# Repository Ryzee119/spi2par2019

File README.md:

# spi2par2019
  
## What is it?
This is a recreation of a legacy Original Xbox adaptor that allowed you to use extremely common and cheap HD44780 compliant character LCD displays with the Xenium modchip SPI interface. The legacy adaptor was called 'spi2par' and has long since been out of production and extremely hard to come by.

I have never had one either, so this design has been made from the ground up.

There are two PCB layouts in this repository:

1. More faithful to the legacy spi2par design.
2. An LCD backpack design that takes advantage of the standard pinout of most HD44780 LCD displays to minimise the amount of wiring needed.

These two layouts are shown in the below photo. The LCD backpack has two pin arrangements so can be used on the two common LCD pin header layouts as shown installed. The intent is to make this as open and easily accessible to anyone with minimal experience in soldering and programming.  

## Features
1. Converts the Xenium SPI interface to HD44780 compliant parallel LCDs. These are extremely cheap and readily available LCD modules.
2. Software controllable brightness
3. Software controllable contrast
4. This feature never existed in the legacy. You can connect two additional wires to the motherboard LPC header, and the board will read fan speed and MB/CPU temperatures directly from the Xbox System Management bus. It will display and update this mid-game. Traditionally the LCD will just pause until you renter the dashboard.  Example below:  

## Assembly and Materials Required
There is two ways you can do this. Option 1 is the intended way and has a PCB daughter board to make installation easier.  <br> The second option uses less components but requires more wiring.

#### Option 1 - Arduino module and PCB adaptor
The standard design

|Part|Qty | Possible Source|
|--|--|--|
| Ryzee119's spi2par2019 PCB |1| OSHPark (Bit expensive, 3 boards):  [spi2par2019backpack](https://oshpark.com/shared_projects/HGCRYTFI) OR<br> [spi2par2019faithful](https://oshpark.com/shared_projects/7YvM7Fwu)  <br>Or, Download the required zip file from the [Gerbers Folder](https://github.com/Ryzee119/spi2par2019/tree/master/hardware/gerbers) and upload the zip file to their online ordering service. Use the following PCB properties: <br> `2 layers, 45x30mm, 1.6mm thick, HASL, 1oz copper, no castellated holes`| 
| Arduino Pro Micro Leonardo 5V/16Mhz |1| [Any clones will work](https://www.aliexpress.com/item/New-Pro-Micro-for-arduino-ATmega32U4-5V-16MHz-Module-with-2-row-pin-header-For-Leonardo/32768308647.html). Make sure they're the 5V/16Mhz variant. | 
| N-Channel MOSFET 2N7002 SOT23 at position Q1| 1 |Find anywhere convenient <br> [Digikey](https://www.digikey.com.au/short/p4zbn8)<br> [Aliexpress](https://www.aliexpress.com/item/Free-Shipping-200PCS-2N7002-MOSFET-N-CH-60V-300MA-SOT-23/897983645.html) |
| JST SH1.0 10 pin 1mm connector (To connect to Xenium) | 1 |Digikey: [Connector](https://www.digikey.com.au/product-detail/en/jst-sales-america-inc/SHR-10V-S-B/455-1385-ND/759874) + 3x[Jumpers](https://www.digikey.com.au/product-detail/en/jst-sales-america-inc/ASSHSSH28K152/455-3076-ND/6009452) OR <br> Aliexpress: [Connector with Jumpers (Get the 10P one)](https://www.aliexpress.com/item/5PCS-100MM-SH-1-0-Wire-Cable-Connector-DIY-SH1-0-JST-2-3-4-5/32952366214.html)|
| General Hook-up Wire 26AWG or so| A metre or two |-|

#### Option 2 - Arduino module only
No extra PCB required, no backlight control, slightly harder soldering

|Part|Qty | Possible Source|
|--|--|--|
| Arduino Pro Micro Leonardo 5V/16Mhz |1| [Any clones will work](https://www.aliexpress.com/item/32768308647.html). Make sure they're the 5V/16Mhz variant. | 
| JST SH1.0 10 pin 1mm connector (To connect to Xenium) | 1 |Digikey: [Connector](https://www.digikey.com.au/product-detail/en/jst-sales-america-inc/SHR-10V-S-B/455-1385-ND/759874) + 3x[Jumpers](https://www.digikey.com.au/product-detail/en/jst-sales-america-inc/ASSHSSH28K152/455-3076-ND/6009452) OR <br> Aliexpress: [Connector with Jumpers (Get the 10P one)](https://www.aliexpress.com/item/32952366214.html)|
| General Hook-up Wire 26AWG or so| A metre or two |-|

## Programming
1. Clone this repository to your PC
2. Download then install the [Arduino IDE](https://www.arduino.cc/en/Main/Software).
3. Copy `spi2par2019` to your Sketch folder and open the `.ino` file.
4. Set the Board Type the `Arduino Leonardo` and the comport correctly.
5. Compile by clicking the tick in the top left.
5. Confirm it has compiled successfully from the console output.  
6. Connect a MicroUSB cable between the Arduino Module and the PC.   
7. Click the upload button and confirm successful. The LCD backlight should come on but no text will be displayed until connected to a Xenium or the Xbox SMBus.

## Installation

## Alternative Installation

## Further Setup
If using XBMC, there appears to be a bug in the way the large text is printed to the LCD screen when used with a Xenium. This can cause the LCD screen to stop working when the screen saver starts.
It is recommended to edit the /system/UserData/LCD.xml file and replace instances of `LCD.TimeWide21` or `LCD.TimeWide22` with something different. Perhaps `LCD.cputemperature` and `LCD.gputemperature` or if you want time, use the standard font (`System.Time`).

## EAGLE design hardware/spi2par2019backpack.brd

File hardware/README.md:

# spi2par2019

All PCBs have been design using [Autodesk Eagle](https://www.autodesk.com/products/eagle/free-download) software.
This has been released as open source hardware released under the CERN Open Hardware Licence v1.2, <br><br><br>

CERN Open Hardware Licence v1.2 

Preamble

Through this CERN Open Hardware Licence ("CERN OHL") version 1.2, CERN
wishes to provide a tool to foster collaboration and sharing among
hardware designers.  The CERN OHL is copyright CERN. Anyone is welcome
to use the CERN OHL, in unmodified form only, for the distribution of
their own Open Hardware designs. Any other right is reserved. Release
of hardware designs under the CERN OHL does not constitute an
endorsement of the licensor or its designs nor does it imply any
involvement by CERN in the development of such designs.

1. Definitions

In this Licence, the following terms have the following meanings:
 
“Licence” means this CERN OHL.

“Documentation” means schematic diagrams, designs, circuit or circuit
board layouts, mechanical drawings, flow charts and descriptive text,
and other explanatory material that is explicitly stated as being made
available under the conditions of this Licence. The Documentation may
be in any medium, including but not limited to computer files and
representations on paper, film, or any other media.

“Documentation Location” means a location where the Licensor has
placed Documentation, and which he believes will be publicly
accessible for at least three years from the first communication to
the public or distribution of Documentation.

“Product” means either an entire, or any part of a, device built using
the Documentation or the modified Documentation.

“Licensee” means any natural or legal person exercising rights under
this Licence.

“Licensor” means any natural or legal person that creates or modifies
Documentation and subsequently communicates to the public and/ or
distributes the resulting Documentation under the terms and conditions
of this Licence.

A Licensee may at the same time be a Licensor, and vice versa. 

Use of the masculine gender includes the feminine and neuter genders
and is employed solely to facilitate reading.

2. Applicability

2.1. This Licence governs the use, copying, modification,
communication to the public and distribution of the Documentation, and
the manufacture and distribution of Products. By exercising any right
granted under this Licence, the Licensee irrevocably accepts these
terms and conditions.

2.2. This Licence is granted by the Licensor directly to the Licensee,
and shall apply worldwide and without limitation in time. The Licensee
may assign his licence rights or grant sub-licences.

2.3. This Licence does not extend to software, firmware, or code
loaded into programmable devices which may be used in conjunction with
the Documentation, the modified Documentation or with Products, unless
such software, firmware, or code is explicitly expressed to be subject
to this Licence. The use of such software, firmware, or code is
otherwise subject to the applicable licence terms and conditions.

3. Copying, modification, communication to the public and distribution
of the Documentation

3.1. The Licensee shall keep intact all copyright and trademarks
notices, all notices referring to Documentation Location, and all
notices that refer to this Licence and to the disclaimer of warranties
that are included in the Documentation. He shall include a copy
thereof in every copy of the Documentation or, as the case may be,
modified Documentation, that he communicates to the public or
distributes.

3.2. The Licensee may copy, communicate to the public and distribute
verbatim copies of the Documentation, in any medium, subject to the
requirements specified in section 3.1.

3.3. The Licensee may modify the Documentation or any portion thereof
provided that upon modification of the Documentation, the Licensee
shall make the modified Documentation available from a Documentation
Location such that it can be easily located by an original Licensor
once the Licensee communicates to the public or distributes the
modified Documentation under section 3.4, and, where required by
section 4.1, by a recipient of a Product. However, the Licensor shall
not assert his rights under the foregoing proviso unless or until a
Product is distributed.

3.4. The Licensee may communicate to the public and distribute the
modified Documentation (thereby in addition to being a Licensee also
becoming a Licensor), always provided that he shall:

a) comply with section 3.1;

b) cause the modified Documentation to carry prominent notices stating
that the Licensee has modified the Documentation, with the date and
description of the modifications;

c) cause the modified Documentation to carry a new Documentation
Location notice if the original Documentation provided for one;

d) make available the modified Documentation at the same level of
abstraction as that of the Documentation, in the preferred format for
making modifications to it (e.g. the native format of the CAD tool as
applicable), and in the event that format is proprietary, in a format
viewable with a tool licensed under an OSI-approved license if the
proprietary tool can create it; and

e) license the modified Documentation under the terms and conditions
of this Licence or, where applicable, a later version of this Licence
as may be issued by CERN.

3.5. The Licence includes a non-exclusive licence to those patents or
registered designs that are held by, under the control of, or
sub-licensable by the Licensor, to the extent necessary to make use of
the rights granted under this Licence. The scope of this section 3.5
shall be strictly limited to the parts of the Documentation or
modified Documentation created by the Licensor.

4. Manufacture and distribution of Products

4.1. The Licensee may manufacture or distribute Products always
provided that, where such manufacture or distribution requires a
licence under this Licence the Licensee provides to each recipient of
such Products an easy means of accessing a copy of the Documentation
or modified Documentation, as applicable, as set out in section 3.

4.2. The Licensee is invited to inform any Licensor who has indicated
his wish to receive this information about the type, quantity and
dates of production of Products the Licensee has (had) manufactured

5. Warranty and liability

5.1. DISCLAIMER – The Documentation and any modified Documentation are
provided "as is" and any express or implied warranties, including, but
not limited to, implied warranties of merchantability, of satisfactory
quality, non-infringement of third party rights, and fitness for a
particular purpose or use are disclaimed in respect of the
Documentation, the modified Documentation or any Product. The Licensor
makes no representation that the Documentation, modified
Documentation, or any Product, does or will not infringe any patent,
copyright, trade secret or other proprietary right. The entire risk as
to the use, quality, and performance of a Product shall be with the
Licensee and not the Licensor. This disclaimer of warranty is an
essential part of this Licence and a condition for the grant of any
rights granted under this Licence. The Licensee warrants that it does
not act in a consumer capacity.

5.2. LIMITATION OF LIABILITY – The Licensor shall have no liability
for direct, indirect, special, incidental, consequential, exemplary,
punitive or other damages of any character including, without
limitation, procurement of substitute goods or services, loss of use,
data or profits, or business interruption, however caused and on any
theory of contract, warranty, tort (including negligence), product
liability or otherwise, arising in any way in relation to the
Documentation, modified Documentation and/or the use, manufacture or
distribution of a Product, even if advised of the possibility of such
damages, and the Licensee shall hold the Licensor(s) free and harmless
from any liability, costs, damages, fees and expenses, including
claims by third parties, in relation to such use.

6. General

6.1. Except for the rights explicitly granted hereunder, this Licence
does not imply or represent any transfer or assignment of intellectual
property rights to the Licensee.

6.2. The Licensee shall not use or make reference to any of the names
(including acronyms and abbreviations), images, or logos under which
the Licensor is known, save in so far as required to comply with
section 3. Any such permitted use or reference shall be factual and
shall in no event suggest any kind of endorsement by the Licensor or
its personnel of the modified Documentation or any Product, or any
kind of implication by the Licensor or its personnel in the
preparation of the modified Documentation or Product.

6.3. CERN may publish updated versions of this Licence which retain
the same general provisions as this version, but differ in detail so
far this is required and reasonable. New versions will be published
with a unique version number.

6.4. This Licence shall terminate with immediate effect, upon written
notice and without involvement of a court if the Licensee fails to
comply with any of its terms and conditions, or if the Licensee
initiates legal action against Licensor in relation to this
Licence. Section 5 shall continue to apply.

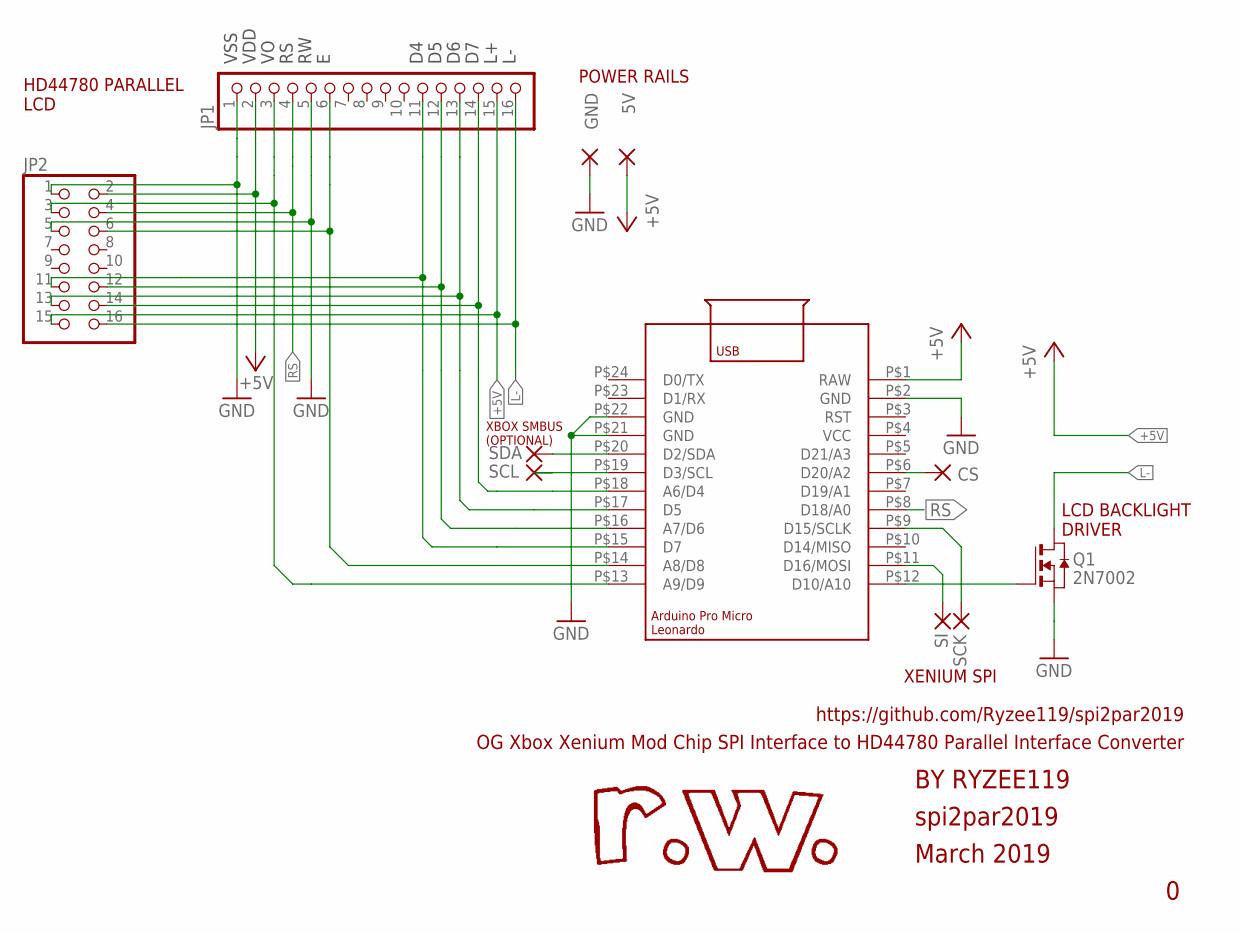
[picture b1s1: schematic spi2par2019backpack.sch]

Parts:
5V: WIREPADSMD1,27-254; SMD1,27-2,54
CS: WIREPADSMD1,27-254; SMD1,27-2,54
GND: WIREPADSMD1,27-254; SMD1,27-2,54
JP1: PINHD-1X16; 1X16
JP2: PINHD-2X8; 2X08
Q1: 2N70026Ω; SOT-23
SCK: WIREPADSMD1,27-254; SMD1,27-2,54
SCL: WIREPADSMD1,27-254; SMD1,27-2,54
SDA: WIREPADSMD1,27-254; SMD1,27-2,54
SI: WIREPADSMD1,27-254; SMD1,27-2,54
U1: ARDUINO_LEONARDO_MICRO

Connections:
+5V: 5V.1, JP1.2, JP1.15, JP2.2, JP2.15, U1.P$1 (RAW)
D4: JP1.11, JP2.11, U1.P$15 (D7)
D5: JP1.12, JP2.12, U1.P$16 (A7/D6)
D6: JP1.13, JP2.13, U1.P$17 (D5)
D7: JP1.14, JP2.14, U1.P$18 (A6/D4)
E: JP1.6, JP2.6, U1.P$14 (A8/D8)
GND: GND.1, JP1.1, JP1.5, JP2.1, JP2.5, Q1.2 (S), U1.P$2 (GND), U1.P$21 (GND), U1.P$22 (GND)
L-: JP1.16, JP2.16, Q1.1 (D)
unnamed: SCL.1, U1.P$19 (D3/SCL)
unnamed: CS.1, U1.P$6 (D20/A2)
unnamed: SCK.1, U1.P$9 (D15/SCLK)
unnamed: SI.1, U1.P$11 (D16/MOSI)
unnamed: Q1.3 (G), U1.P$12 (D10/A10)
unnamed: SDA.1, U1.P$20 (D2/SDA)
RS: JP1.4, JP2.4, U1.P$8 (D18/A0)
VO: JP1.3, JP2.3, U1.P$13 (A9/D9)

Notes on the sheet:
spi2par2019
March 2019
BY RYZEE119
OG Xbox Xenium Mod Chip SPI Interface to HD44780 Parallel Interface Converter
https://github.com/Ryzee119/spi2par2019
HD44780 PARALLEL LCD
POWER RAILS
LCD BACKLIGHT DRIVER
XENIUM SPI
XBOX SMBUS (OPTIONAL)
2N7002
VSS
VDD

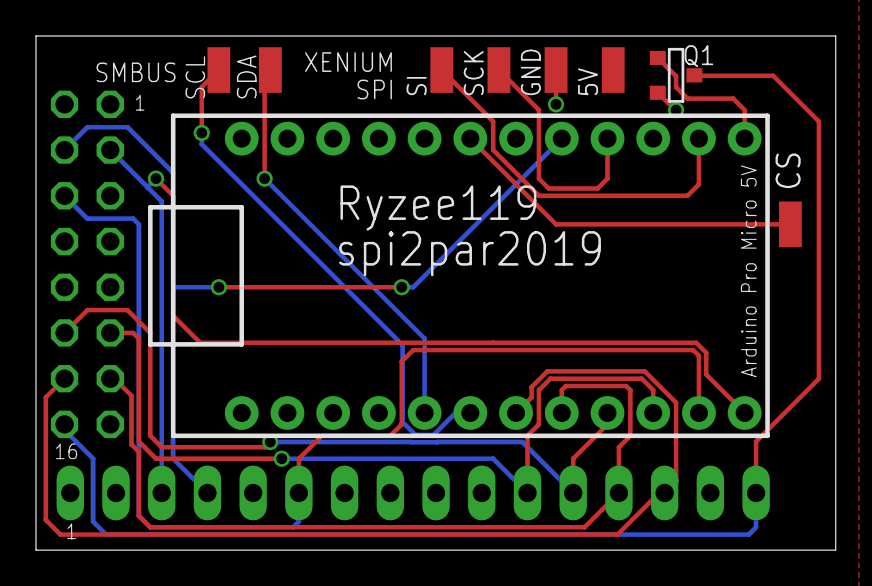
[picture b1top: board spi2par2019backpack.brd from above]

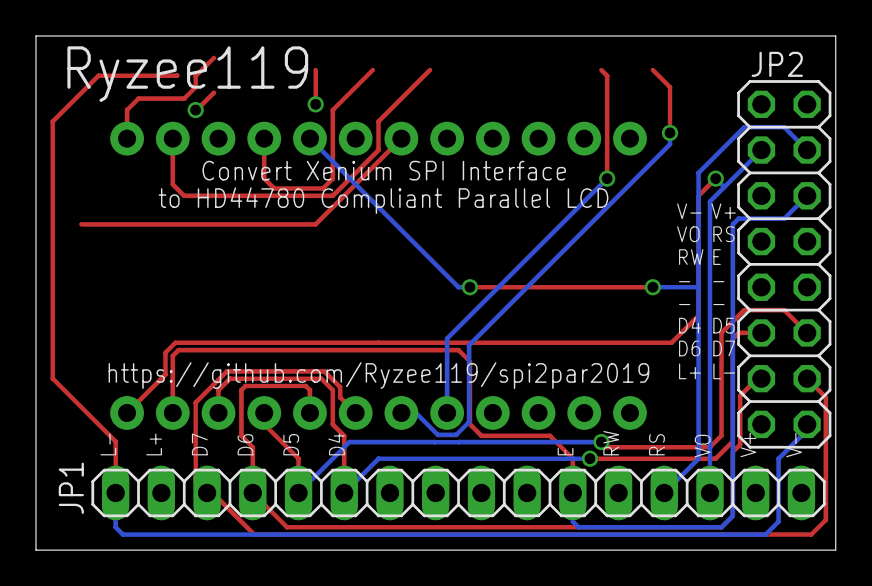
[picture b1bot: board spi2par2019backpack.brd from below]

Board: 2 copper layers, 44.4 x 28.6 mm, 11 parts (2 on the bottom side), 16 nets.

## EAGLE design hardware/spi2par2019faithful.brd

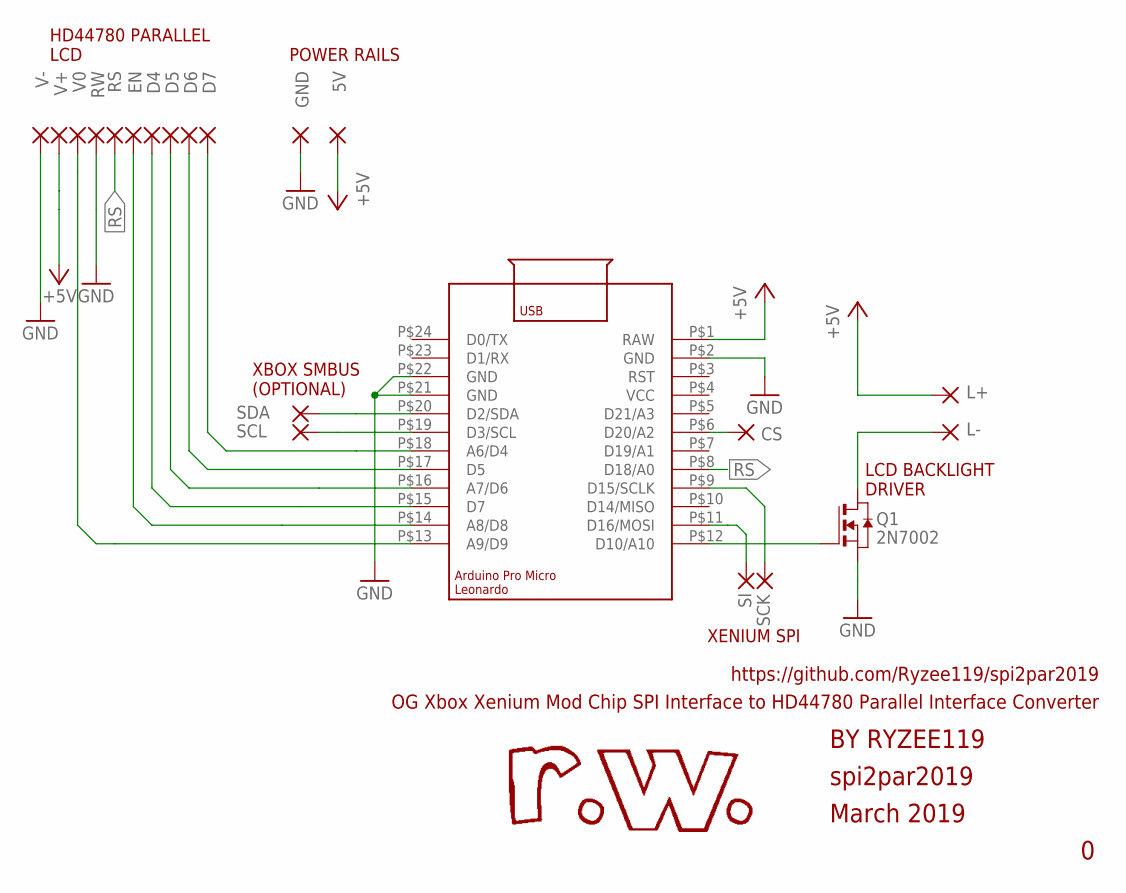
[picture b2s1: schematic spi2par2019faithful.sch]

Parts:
5V: WIREPADSMD1,27-254; SMD1,27-2,54
CS: WIREPADSMD1,27-254; SMD1,27-2,54
D4, D5, D6, D7: WIREPADSMD1,27-254; SMD1,27-2,54
EN: WIREPADSMD1,27-254; SMD1,27-2,54
GND: WIREPADSMD1,27-254; SMD1,27-2,54
L+: WIREPADSMD1,27-254; SMD1,27-2,54
L-: WIREPADSMD1,27-254; SMD1,27-2,54
Q1: 2N70026Ω; SOT-23
RS: WIREPADSMD1,27-254; SMD1,27-2,54
RW: WIREPADSMD1,27-254; SMD1,27-2,54
SCK: WIREPADSMD1,27-254; SMD1,27-2,54
SCL: WIREPADSMD1,27-254; SMD1,27-2,54
SDA: WIREPADSMD1,27-254; SMD1,27-2,54
SI: WIREPADSMD1,27-254; SMD1,27-2,54
U1: ARDUINO_LEONARDO_MICRO
V0: WIREPADSMD1,27-254; SMD1,27-2,54
V+: WIREPADSMD1,27-254; SMD1,27-2,54
V-: WIREPADSMD1,27-254; SMD1,27-2,54

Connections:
+5V: 5V.1, L+.1, U1.P$1 (RAW), V+.1
GND: GND.1, Q1.2 (S), RW.1, U1.P$2 (GND), U1.P$21 (GND), U1.P$22 (GND), V-.1
unnamed: SCL.1, U1.P$19 (D3/SCL)
unnamed: CS.1, U1.P$6 (D20/A2)
unnamed: SCK.1, U1.P$9 (D15/SCLK)
unnamed: SI.1, U1.P$11 (D16/MOSI)
unnamed: D7.1, U1.P$18 (A6/D4)
unnamed: D6.1, U1.P$17 (D5)
unnamed: D5.1, U1.P$16 (A7/D6)
unnamed: D4.1, U1.P$15 (D7)
unnamed: EN.1, U1.P$14 (A8/D8)
unnamed: Q1.3 (G), U1.P$12 (D10/A10)
unnamed: U1.P$13 (A9/D9), V0.1
unnamed: L-.1, Q1.1 (D)
unnamed: SDA.1, U1.P$20 (D2/SDA)
RS: RS.1, U1.P$8 (D18/A0)

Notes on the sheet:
spi2par2019
March 2019
BY RYZEE119
OG Xbox Xenium Mod Chip SPI Interface to HD44780 Parallel Interface Converter
https://github.com/Ryzee119/spi2par2019
HD44780 PARALLEL LCD
POWER RAILS
LCD BACKLIGHT DRIVER
XENIUM SPI
XBOX SMBUS (OPTIONAL)
2N7002

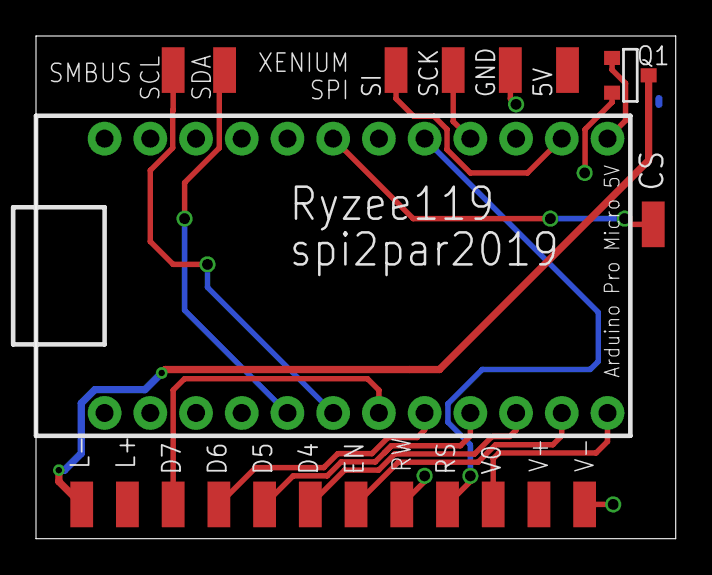
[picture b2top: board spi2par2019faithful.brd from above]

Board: 2 copper layers, 35.5 x 27.9 mm, 21 parts (0 on the bottom side), 16 nets.

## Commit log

2019-05-03 Fixes and additional info added
2019-05-17 Fixed 1.6 temp readout, added Conexant video resolution output
2019-05-18 Added Programming and Install Instructions, typos fixed. 1.6 temp readout fixed
2019-05-18 Added CERN license
2019-05-29 Fixed Fahrenheit display
2019-09-01 Fixed PWM flickering issue
2019-09-15 Fixed Fahrenheit display on non 1.6 versions
2019-10-28 Slight speed tweak on hd44780, code clean up
2019-12-05 Remove unused files
2019-12-06 Added XeniumCursorHome and many bug fixes. Better stability during boot up
2020-07-01 Fix some compiler warnings and print bugs
2020-08-24 Add github actions build
2020-08-24 Add LiquidCrystal lib
2020-08-24 Enable compiler warnings
2020-08-24 Add build build to readme and simplify text
2020-08-24 Improve programming order
2021-06-03 Revert "Update spi2par2019.ino"
    This reverts commit 0e3ad35cb1308a0ac55b05b96bcff4d582e24928.
2021-06-03 Update to define LCD size
    Update to allow LCD size to be defined. Corrects formatting of SMBus read data and properly initializes LCD.
2021-06-07 Fixed macros
2021-06-07 CI: Update latest arduino CLI
2021-06-07 Updating to allow LCD size definition. (#7)
    Allow configurable LCD size
2021-06-30 Build: Allow re-running build
